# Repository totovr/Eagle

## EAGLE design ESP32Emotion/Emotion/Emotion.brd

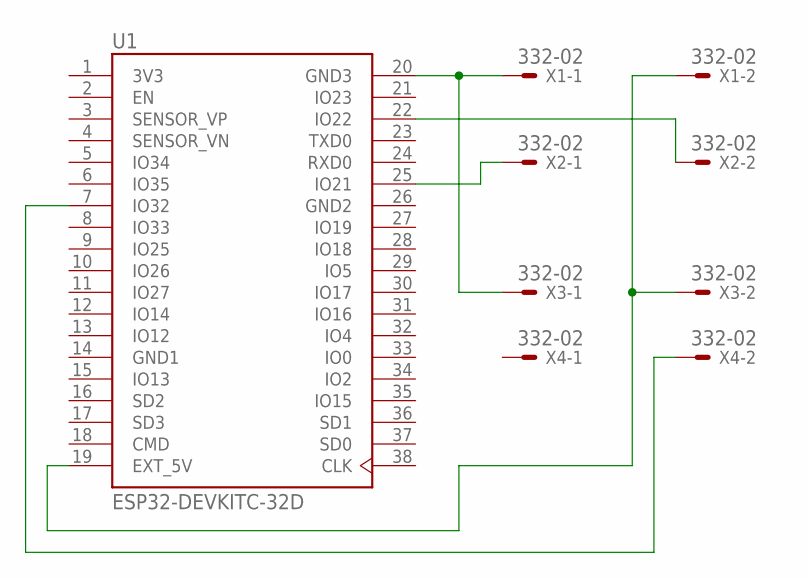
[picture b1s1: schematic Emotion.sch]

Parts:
U1: ESP32-DEVKITC-32D; MODULE_ESP32-DEVKITC-32D
X1, X2, X3, X4: 332-02

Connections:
3V3: U1.1 (3V3)
GND1: U1.14 (GND1)
GND2: U1.26 (GND2)
unnamed: U1.20 (GND3), X1.1, X3.1
unnamed: U1.19 (EXT_5V), X1.2, X3.2
unnamed: U1.25 (IO21), X2.1
unnamed: U1.22 (IO22), X2.2
unnamed: U1.7 (IO32), X4.2

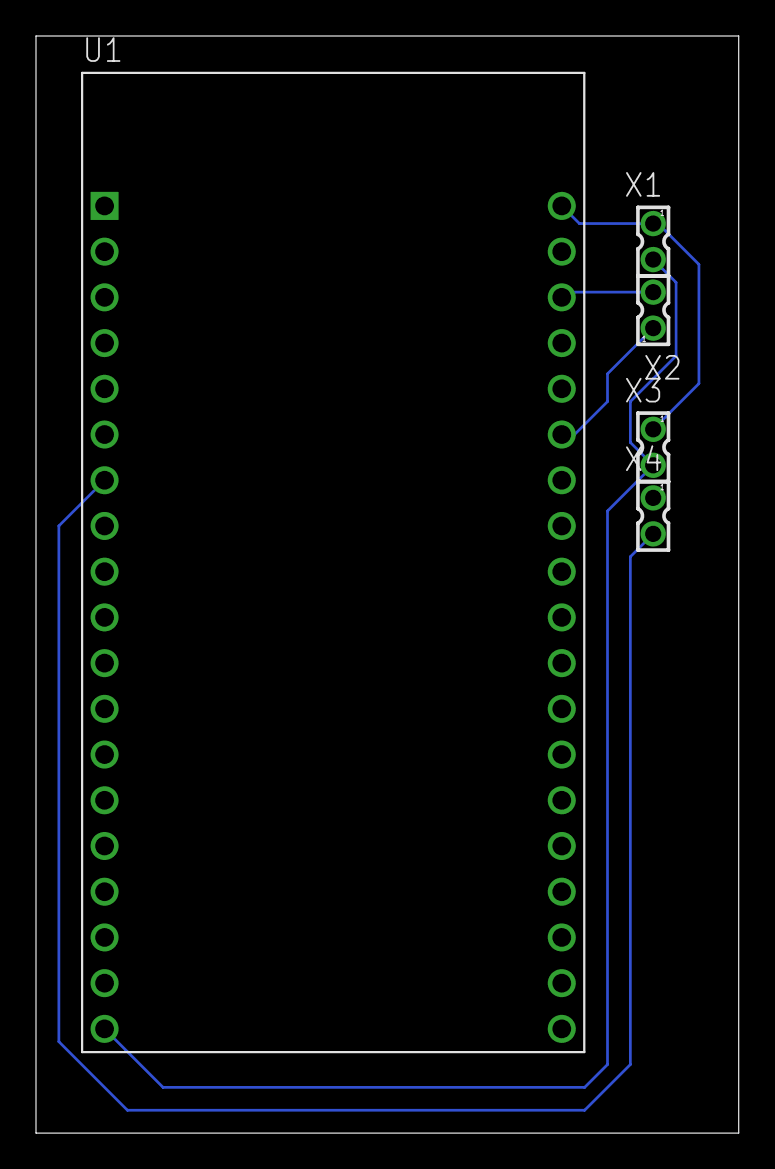
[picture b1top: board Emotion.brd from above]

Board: 2 copper layers, 39.0 x 61.0 mm, 5 parts (0 on the bottom side), 5 nets.

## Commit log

2019-01-23 Emotion board
